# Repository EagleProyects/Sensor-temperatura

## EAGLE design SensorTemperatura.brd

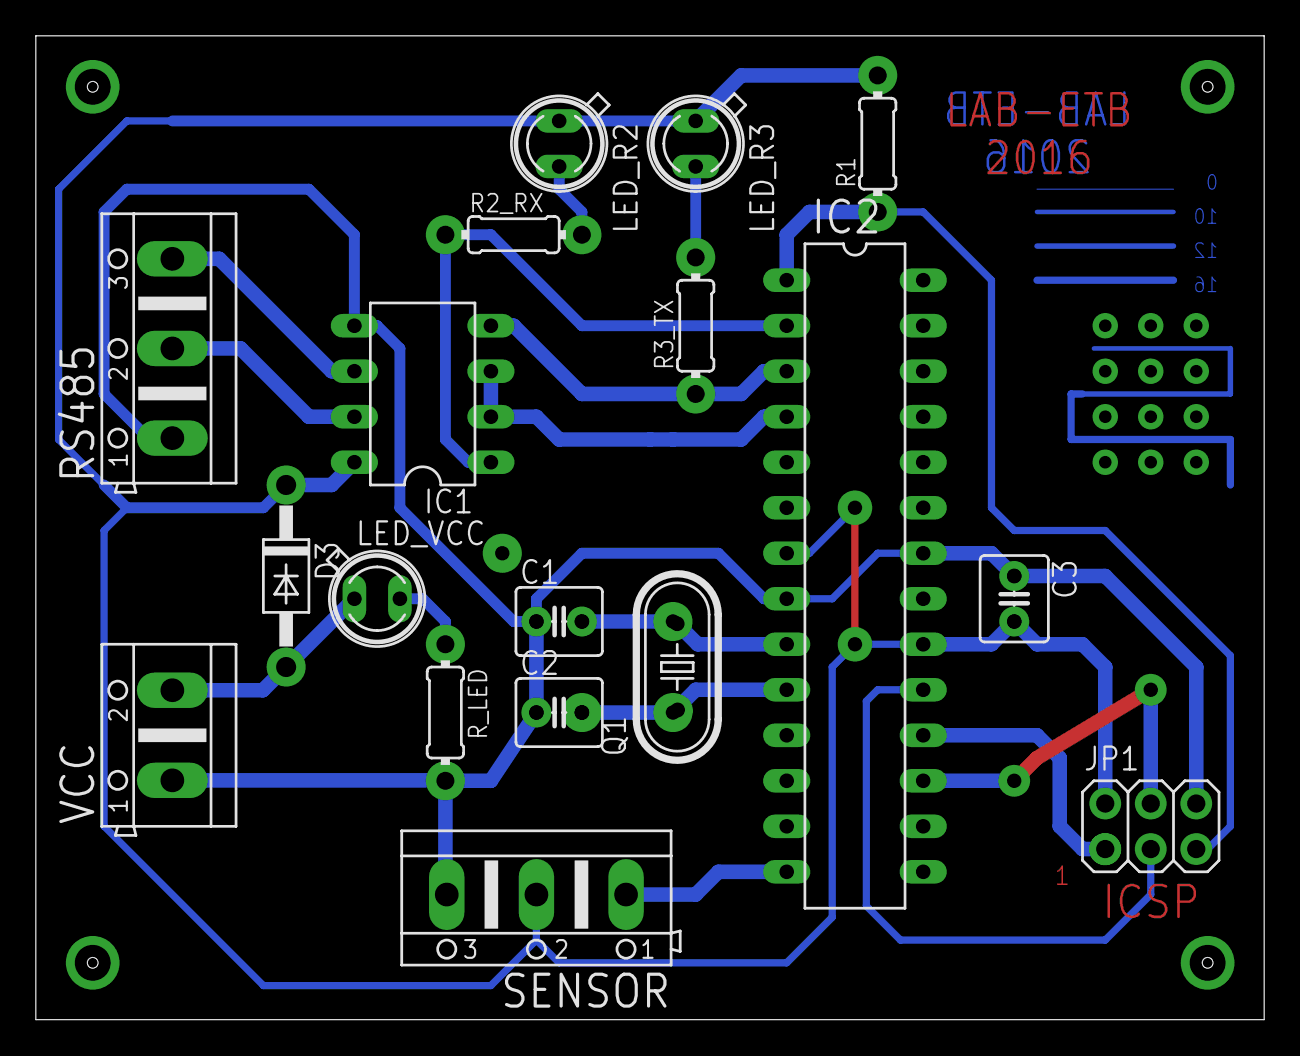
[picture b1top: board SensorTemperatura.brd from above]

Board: 2 copper layers, 68.6 x 54.9 mm, 18 parts (0 on the bottom side), 18 nets.

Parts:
C1, C2: 22nf; C025-040X050
C3: .1nf; C025-040X050
D3: 1N4004; DO41-10
IC1: MAX481CPA; DIL08
IC2: MEGA8-P; DIL28-3
JP1: 2X03
LED_R2, LED_R3: SFH482
LED_VCC: SFH482
Q1: 16mhz; HC49U-V
R1, R2_RX, R3_TX: 0204/7
RS485: AK500/3
R_LED: 0204/7
SENSOR: AK500/3
VCC: AK500/2

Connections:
GND: C1.1, C2.1, C3.1, IC1.5, IC2.8, IC2.22, JP1.6, R_LED.2, SENSOR.3, VCC.1
unnamed: IC1.2, IC1.3, IC2.4
unnamed: IC2.18, JP1.1
unnamed: IC1.1, IC2.2, R2_RX.1
unnamed: LED_R2.K, R2_RX.2
unnamed: LED_R3.K, R3_TX.2
unnamed: IC1.4, IC2.3, R3_TX.1
unnamed: IC1.6, RS485.3
unnamed: IC1.7, RS485.2
unnamed: IC2.19, JP1.3
unnamed: IC2.14, SENSOR.1
unnamed: C1.2, IC2.9, Q1.2
unnamed: C2.2, IC2.10, Q1.1
unnamed: IC2.1, JP1.5, R1.1
unnamed: IC2.17, JP1.4
unnamed: D3.A, LED_VCC.A, VCC.2
unnamed: LED_VCC.K, R_LED.1
VCC: C3.2, D3.C, IC1.8, IC2.7, IC2.20, JP1.2, LED_R2.A, LED_R3.A, R1.2, SENSOR.2

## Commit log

2016-03-09 :boom::camel: Added .gitattributes & .gitignore files
2016-03-09 add changes
2016-05-05 terrena
    pcb
2016-05-05 fix terrena
